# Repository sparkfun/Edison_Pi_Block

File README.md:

SparkFun Edison Pi Block
========================

[*SparkFun Edison GPIO Breakout (DEV-13044)*](https://www.sparkfun.com/products/13038)

The Pi Block is a simple breakout board to bring the GPIO from the Intel Edison to the user. The Block provides level-shifted access to basic GPIO, PWM, UART, I<sup>2</sup>C, and SPI. The pins are presented in the same configuration as a [Raspberry Pi Model B header](http://elinux.org/RPi_Low-level_peripherals#Model_A_and_B_.28Original.29).

Access to the GPIO pins can be accomplished through [MRAA](https://github.com/intel-iot-devkit/mraa). The GPIO number listed on the board or Linux is not the same as MRAA. Refer to the table to see which GPIO pin maps to which number in MRAA. 

*MRAA pin map table based on [Intel's IOT Dev Kit Repository](https://github.com/intel-iot-devkit/mraa/blob/master/docs/edison.md)*

*Pins on the Pi Block are denoted with a * after the GP number*

<table class="table table-bordered">
<thead><tr><th class="text-center" title="Field #1">Edison Pin (Linux)</th>
<th class="text-center" title="Field #2">Arduino Breakout</th>
<th class="text-center" title="Field #3">Mini Breakout</th>
<th class="text-center" title="Field #4">MRAA Number</th>
<th class="text-center" title="Field #5">Pinmode0</th>
<th class="text-center" title="Field #6">Pinmode1</th>
<th class="text-center" title="Field #7">Pinmode2</th>
</tr></thead>
<tbody><tr class="warning" align="center"><td>GP12*</td>
<td>3</td>
<td>J18-7 </td>
<td align="right">20</td>
<td>GPIO-12</td>
<td>PWM0</td>
<td> </td>
</tr>
<tr class="warning" align="center"><td>GP13*</td>
<td>5</td>
<td>J18-1 </td>
<td align="right">14</td>
<td>GPIO-13</td>
<td>PWM1</td>
<td> </td>
</tr>
<tr class="warning" align="center"><td>GP14*</td>
<td>A4</td>
<td>J19-9 </td>
<td align="right">36</td>
<td>GPIO-14</td>
<td> </td>
<td> </td>
</tr>
<tr align="center"><td>GP15</td>
<td> </td>
<td>J20-7 </td>
<td align="right">48</td>
<td>GPIO-15</td>
<td> </td>
<td> </td>
</tr>
<tr class="warning" align="center"><td>GP19*</td>
<td> </td>
<td>J18-6 </td>
<td align="right">19</td>
<td>GPIO-19</td>
<td>I2C-1-SCL</td>
<td> </td>
</tr>
<tr class="warning" align="center"><td>GP20*</td>
<td> </td>
<td>J17-8 </td>
<td align="right">7</td>
<td>GPIO-20</td>
<td>I2C-1-SDA</td>
<td> </td>
</tr>
<tr align="center"><td>GP27</td>
<td> </td>
<td>J17-7 </td>
<td align="right">6</td>
<td>GPIO-27</td>
<td>I2C-6-SCL</td>
<td> </td>
</tr>
<tr align="center"><td>GP28</td>
<td> </td>
<td>J17-9 </td>
<td align="right">8</td>
<td>GPIO-28</td>
<td>I2C-6-SDA</td>
<td> </td>
</tr>
<tr align="center"><td>GP40</td>
<td>13</td>
<td>J19-10 </td>
<td align="right">37</td>
<td>GPIO-40</td>
<td>SSP2_CLK</td>
<td> </td>
</tr>
<tr align="center"><td>GP41</td>
<td>10</td>
<td>J20-10 </td>
<td align="right">51</td>
<td>GPIO-41</td>
<td>SSP2_FS</td>
<td> </td>
</tr>
<tr align="center"><td>GP42</td>
<td>12</td>
<td>J20-9 </td>
<td align="right">50</td>
<td>GPIO-42</td>
<td>SSP2_RXD</td>
<td> </td>
</tr>
<tr align="center"><td>GP43</td>
<td>11</td>
<td>J19-11 </td>
<td align="right">38</td>
<td>GPIO-43</td>
<td>SSP2_TXD</td>
<td> </td>
</tr>
<tr class="warning" align="center"><td>GP44*</td>
<td>A0</td>
<td>J19-4 </td>
<td align="right">31</td>
<td>GPIO-44</td>
<td> </td>
<td> </td>
</tr>
<tr class="warning" align="center"><td>GP45*</td>
<td>A1</td>
<td>J20-4 </td>
<td align="right">45</td>
<td>GPIO-45</td>
<td> </td>
<td> </td>
</tr>
<tr class="warning" align="center"><td>GP46*</td>
<td>A2</td>
<td>J19-5 </td>
<td align="right">32</td>
<td>GPIO-46</td>
<td> </td>
<td> </td>
</tr>
<tr class="warning" align="center"><td>GP47*</td>
<td>A3</td>
<td>J20-5 </td>
<td align="right">46</td>
<td>GPIO-47</td>
<td> </td>
<td> </td>
</tr>
<tr class="warning" align="center"><td>GP48*</td>
<td>7</td>
<td>J19-6 </td>
<td align="right">33</td>
<td>GPIO-48</td>
<td> </td>
<td> </td>
</tr>
<tr align="center"><td>GP49</td>
<td>8</td>
<td>J20-6 </td>
<td align="right">47</td>
<td>GPIO-49</td>
<td> </td>
<td> </td>
</tr>
<tr align="center"><td>GP77</td>
<td> </td>
<td>J19-12 </td>
<td align="right">39</td>
<td>GPIO-77</td>
<td>SD</td>
<td> </td>
</tr>
<tr align="center"><td>GP78</td>
<td> </td>
<td>J20-11 </td>
<td align="right">52</td>
<td>GPIO-78</td>
<td>SD</td>
<td> </td>
</tr>
<tr align="center"><td>GP79</td>
<td> </td>
<td>J20-12 </td>
<td align="right">53</td>
<td>GPIO-79</td>
<td>SD</td>
<td> </td>
</tr>
<tr align="center"><td>GP80</td>
<td> </td>
<td>J20-13 </td>
<td align="right">54</td>
<td>GPIO-80</td>
<td>SD</td>
<td> </td>
</tr>
<tr align="center"><td>GP81</td>
<td> </td>
<td>J20-14 </td>
<td align="right">55</td>
<td>GPIO-81</td>
<td>SD</td>
<td> </td>
</tr>
<tr align="center"><td>GP82</td>
<td> </td>
<td>J19-13 </td>
<td align="right">40</td>
<td>GPIO-82</td>
<td>SD</td>
<td> </td>
</tr>
<tr align="center"><td>GP83</td>
<td> </td>
<td>J19-14 </td>
<td align="right">41</td>
<td>GPIO-83</td>
<td>SD</td>
<td> </td>
</tr>
<tr align="center"><td>GP84</td>
<td> </td>
<td>J20-8 </td>
<td align="right">49</td>
<td>GPIO-84</td>
<td>SD</td>
<td> </td>
</tr>
<tr class="warning" align="center"><td>GP109*</td>
<td> </td>
<td>J17-11 </td>
<td align="right">10</td>
<td>GPIO-109</td>
<td>SPI-5-SCK</td>
<td> </td>
</tr>
<tr class="warning" align="center"><td>GP110*</td>
<td> </td>
<td>J18-10 </td>
<td align="right">23</td>
<td>GPIO-110</td>
<td>SPI-5-CS0</td>
<td> </td>
</tr>
<tr class="warning" align="center"><td>GP111*</td>
<td> </td>
<td>J17-10 </td>
<td align="right">9</td>
<td>GPIO-111</td>
<td>SPI-5-CS1</td>
<td> </td>
</tr>
<tr class="warning" align="center"><td>GP114*</td>
<td> </td>
<td>J18-11 </td>
<td align="right">24</td>
<td>GPIO-114</td>
<td>SPI-5-MISO</td>
<td> </td>
</tr>
<tr class="warning" align="center"><td>GP115*</td>
<td> </td>
<td>J17-12 </td>
<td align="right">11</td>
<td>GPIO-115</td>
<td>SPI-5-MOSI</td>
<td> </td>
</tr>
<tr align="center"><td>GP128</td>
<td>2</td>
<td>J17-14 </td>
<td align="right">13</td>
<td>GPIO-128</td>
<td>UART-1-CTS</td>
<td> </td>
</tr>
<tr align="center"><td>GP129</td>
<td>4</td>
<td>J18-12 </td>
<td align="right">25</td>
<td>GPIO-129</td>
<td>UART-1-RTS</td>
<td> </td>
</tr>
<tr class="warning" align="center"><td>GP130*</td>
<td>0</td>
<td>J18-13 </td>
<td align="right">26</td>
<td>GPIO-130</td>
<td>UART-1-RX</td>
<td> </td>
</tr>
<tr class="warning" align="center"><td>GP131*</td>
<td>1</td>
<td>J19-8 </td>
<td align="right">35</td>
<td>GPIO-131</td>
<td>UART-1-TX</td>
<td> </td>
</tr>
<tr align="center"><td>GP134</td>
<td> </td>
<td>J20-3 </td>
<td align="right">44</td>
<td> </td>
<td> </td>
<td> </td>
</tr>
<tr align="center"><td>GP135</td>
<td> </td>
<td>J17-5 </td>
<td align="right">4</td>
<td>GPIO-135</td>
<td>UART</td>
<td> </td>
</tr>
<tr align="center"><td>GP165</td>
<td>A5</td>
<td>J18-2 </td>
<td align="right">15</td>
<td>GPIO-165</td>
<td> </td>
<td> </td>
</tr>
<tr align="center"><td>GP182</td>
<td>6</td>
<td>J17-1 </td>
<td align="right">0</td>
<td>GPIO-182</td>
<td>PWM2</td>
<td> </td>
</tr>
<tr align="center"><td>GP183</td>
<td>9</td>
<td>J18-8 </td>
<td align="right">21</td>
<td>GPIO-183</td>
<td>PWM3</td>
<td> </td>
</tr>
</tbody></table>

Repository Contents
-------------------
* **/Hardware** - Eagle PCB layout files
* **/Production** - Files to support SparkFun production

Documentation
--------------
* **[Hookup Guide](https://learn.sparkfun.com/tutorials/sparkfun-blocks-for-intel-edison---pi-block)** - Basic hookup guide

Product Versions
----------------
* [DEV-13044](https://www.sparkfun.com/products/13038)- Hardware version 1.0. 

Version History
---------------
* [V_1.0](https://github.com/sparkfun/Edison_Pi_Block/tree/V_1.0) - GitHub files version 1.0

License Information
-------------------

This product is _**open source**_! 

Please review the LICENSE.md file for license information. 

If you have any questions or concerns on licensing, please contact techsupport@sparkfun.com.

Distributed as-is; no warranty is given.

- Your friends at SparkFun.

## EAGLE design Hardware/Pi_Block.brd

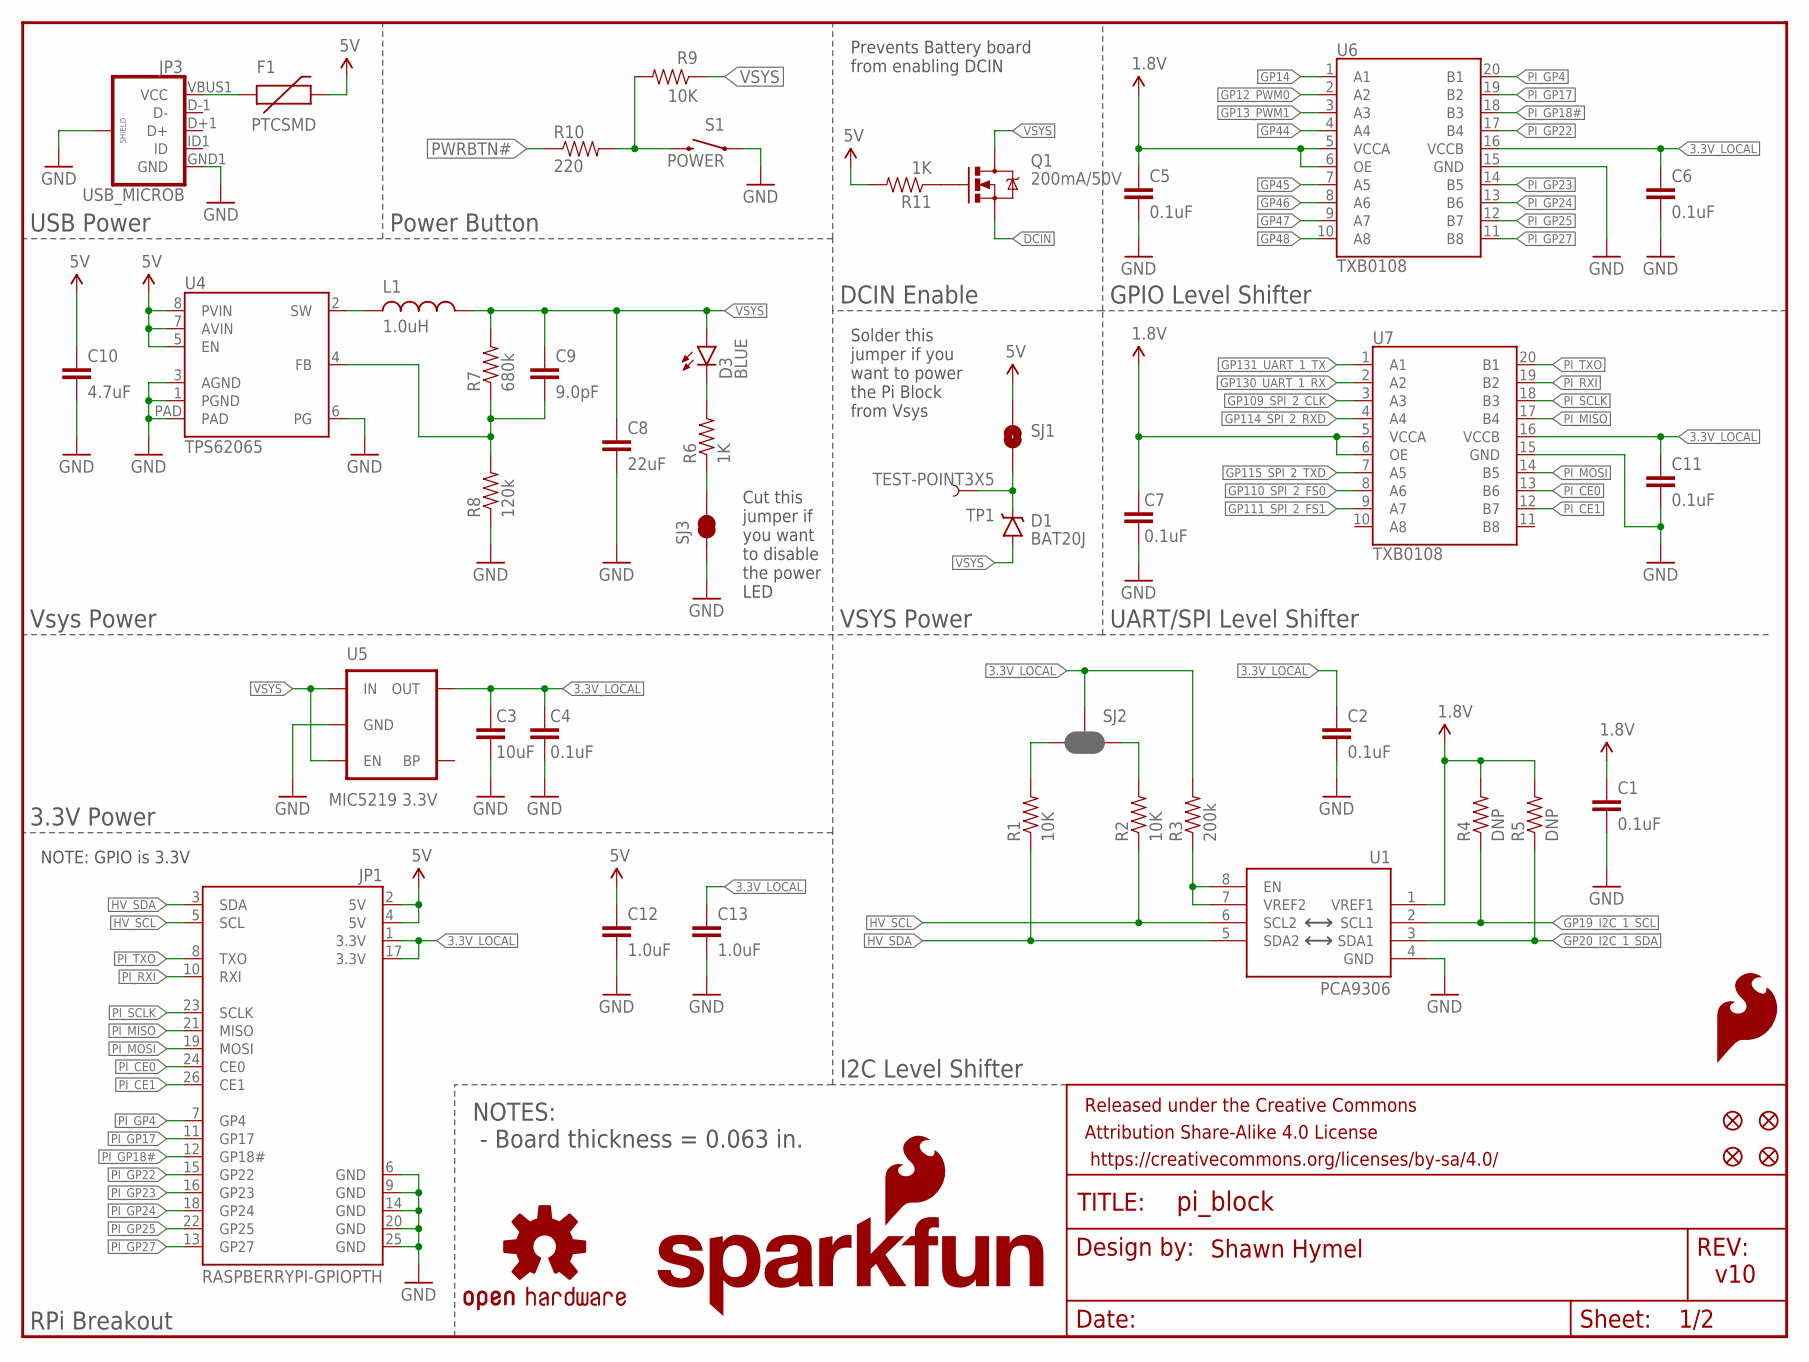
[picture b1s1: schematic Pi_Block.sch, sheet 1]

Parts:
C1, C2, C4, C5, C6, C7, C11: 0.1uF; 0603-CAP
C3: 10uF; 0805
C8: 22uF; 0805
C9: 9.0pF; 0603-CAP
C10: 4.7uF; 0603-CAP
C12, C13: 1.0uF; 0603-CAP
D1: BAT20J; SOD-323
D3: BLUE; LED-0603
F1: PTCSMD; PTC-1206
FID1, FID2, FID3, FID4: FIDUCIAL1X2; FIDUCIAL-1X2
FRAME1, FRAME3: FRAME-LETTER; CREATIVE_COMMONS
JP1: RASPBERRYPI-GPIOPTH; 2X13-SHROUDED
JP3: USB_MICROB; USB-B-MICRO-SMD_V03
L1: 1.0uH; INDUCTOR-SRP4020
LOGO1: OSHW-LOGOS; OSHW-LOGO-S
LOGO3: SFE_LOGO_FLAME.2_INCH; SFE_LOGO_FLAME_.2
LOGO4: SFE_LOGO_NAME_FLAME.1_INCH; SFE_LOGO_NAME_FLAME_.1
Q1: 200mA/50V; SOT23-3
R1, R2, R9: 10K; 0603-RES
R3: 200k; 0603-RES
R4, R5: DNP; 0603-RES
R6, R11: 1K; 0603-RES
R7: 680k; 0603-RES
R8: 120k; 0603-RES
R10: 220; 0603-RES
S1: POWER; TACTILE_SWITCH-SMD-RIGHT-ANGLE
SJ1: JUMPER-PAD-2-NOYES_SILK; PAD-JUMPER-2-NO_YES_SILK
SJ2: JUMPER-PAD-3-NC_BY_PASTE; PAD-JUMPER-3-NC_BY_PASTE_YES_SILK_FULL_BOX
SJ3: JUMPER-PAD-2-NC_BY_TRACE; PAD-JUMPER-2-NC_BY_TRACE_YES_SILK
TP1: TEST-POINT3X5; PAD.03X.05
U1: PCA9306; PCA9306DC-1:1
U4: TPS62065; WSON-8-PAD
U5: MIC5219 3.3V; SOT23-5
U6, U7: TXB0108; UFDFN-20

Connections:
1.8V: C1.1, C5.1, C7.1, R4.2, R5.2, U1.1 (VREF1), U6.5 (VCCA), U6.6 (OE), U7.5 (VCCA), U7.6 (OE); also elsewhere on the board
3.3V_LOCAL: C2.1, C3.1, C4.1, C6.1, C11.1, C13.1, JP1.1 (3.3V), JP1.17 (3.3V), R3.2, SJ2.2, U5.5 (OUT), U6.16 (VCCB), U7.16 (VCCB)
5V: C10.1, C12.1, F1.2, JP1.2 (5V), JP1.4 (5V), R11.2, SJ1.1, U4.5 (EN), U4.7 (AVIN), U4.8 (PVIN)
DCIN: Q1.2 (S); also elsewhere on the board
GND: C1.2, C2.2, C3.2, C4.2, C5.2, C6.2, C7.2, C8.2, C10.2, C11.2, C12.2, C13.2, JP1.6 (GND), JP1.9 (GND), JP1.14 (GND), JP1.20 (GND), JP1.25 (GND), JP3.GND1 (GND), JP3.SHIELD1 (SHIELD), JP3.SHIELD2 (SHIELD), JP3.SHIELD3 (SHIELD), R8.1, S1.1, SJ3.1, U1.4 (GND), U4.1 (PGND), U4.3 (AGND), U4.6 (PG), U4.PAD, U5.2 (GND), U6.15 (GND), U7.15 (GND); also elsewhere on the board
GP12_PWM0: U6.2 (A2); also elsewhere on the board
GP13_PWM1: U6.3 (A3); also elsewhere on the board
GP14: U6.1 (A1); also elsewhere on the board
GP19_I2C_1_SCL: R4.1, U1.2 (SCL1); also elsewhere on the board
GP20_I2C_1_SDA: R5.1, U1.3 (SDA1); also elsewhere on the board
GP44: U6.4 (A4); also elsewhere on the board
GP45: U6.7 (A5); also elsewhere on the board
GP46: U6.8 (A6); also elsewhere on the board
GP47: U6.9 (A7); also elsewhere on the board
GP48: U6.10 (A8); also elsewhere on the board
GP109_SPI_2_CLK: U7.3 (A3); also elsewhere on the board
GP110_SPI_2_FS0: U7.8 (A6); also elsewhere on the board
GP111_SPI_2_FS1: U7.9 (A7); also elsewhere on the board
GP114_SPI_2_RXD: U7.4 (A4); also elsewhere on the board
GP115_SPI_2_TXD: U7.7 (A5); also elsewhere on the board
GP130_UART_1_RX: U7.2 (A2); also elsewhere on the board
GP131_UART_1_TX: U7.1 (A1); also elsewhere on the board
HV_SCL: JP1.5 (SCL), R2.1, U1.6 (SCL2)
HV_SDA: JP1.3 (SDA), R1.1, U1.5 (SDA2)
unnamed: R3.1, U1.7 (VREF2), U1.8 (EN)
unnamed: F1.1, JP3.VBUS1 (VCC)
unnamed: D1.C, SJ1.2, TP1.P$1
unnamed: R1.2, SJ2.3
unnamed: R2.2, SJ2.1
unnamed: D3.C, R6.2
unnamed: R6.1, SJ3.2
unnamed: R9.2, R10.2, S1.2
unnamed: Q1.1 (G), R11.1
unnamed: C9.2, R7.1, R8.2, U4.4 (FB)
unnamed: L1.P$1 (1), U4.2 (SW)
PI_CE0: JP1.24 (CE0), U7.13 (B6)
PI_CE1: JP1.26 (CE1), U7.12 (B7)
PI_GP4: JP1.7 (GP4), U6.20 (B1)
PI_GP17: JP1.11 (GP17), U6.19 (B2)
PI_GP18#: JP1.12 (GP18#), U6.18 (B3)
PI_GP22: JP1.15 (GP22), U6.17 (B4)
PI_GP23: JP1.16 (GP23), U6.14 (B5)
PI_GP24: JP1.18 (GP24), U6.13 (B6)
PI_GP25: JP1.22 (GP25), U6.12 (B7)
PI_GP27: JP1.13 (GP27), U6.11 (B8)
PI_MISO: JP1.21 (MISO), U7.17 (B4)
PI_MOSI: JP1.19 (MOSI), U7.14 (B5)
PI_RXI: JP1.10 (RXI), U7.19 (B2)
PI_SCLK: JP1.23 (SCLK), U7.18 (B3)
PI_TXO: JP1.8 (TXO), U7.20 (B1)
PWRBTN#: R10.1; also elsewhere on the board
VSYS: C8.1, C9.1, D1.A, D3.A, L1.P$2 (2), Q1.3 (D), R7.2, R9.1, U5.1 (IN), U5.3 (EN); also elsewhere on the board

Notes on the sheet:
v10
Shawn Hymel
USB Power
Vsys Power
3.3V Power
RPi Breakout
GPIO Level Shifter
UART/SPI Level Shifter
I2C Level Shifter
Power Button
Prevents Battery board from enabling DCIN
DCIN Enable
VSYS Power
Solder this jumper if you want to power the Pi Block from Vsys
Cut this jumper if you want to disable the power LED
NOTE: GPIO is 3.3V
NOTES: - Board thickness = 0.063 in.

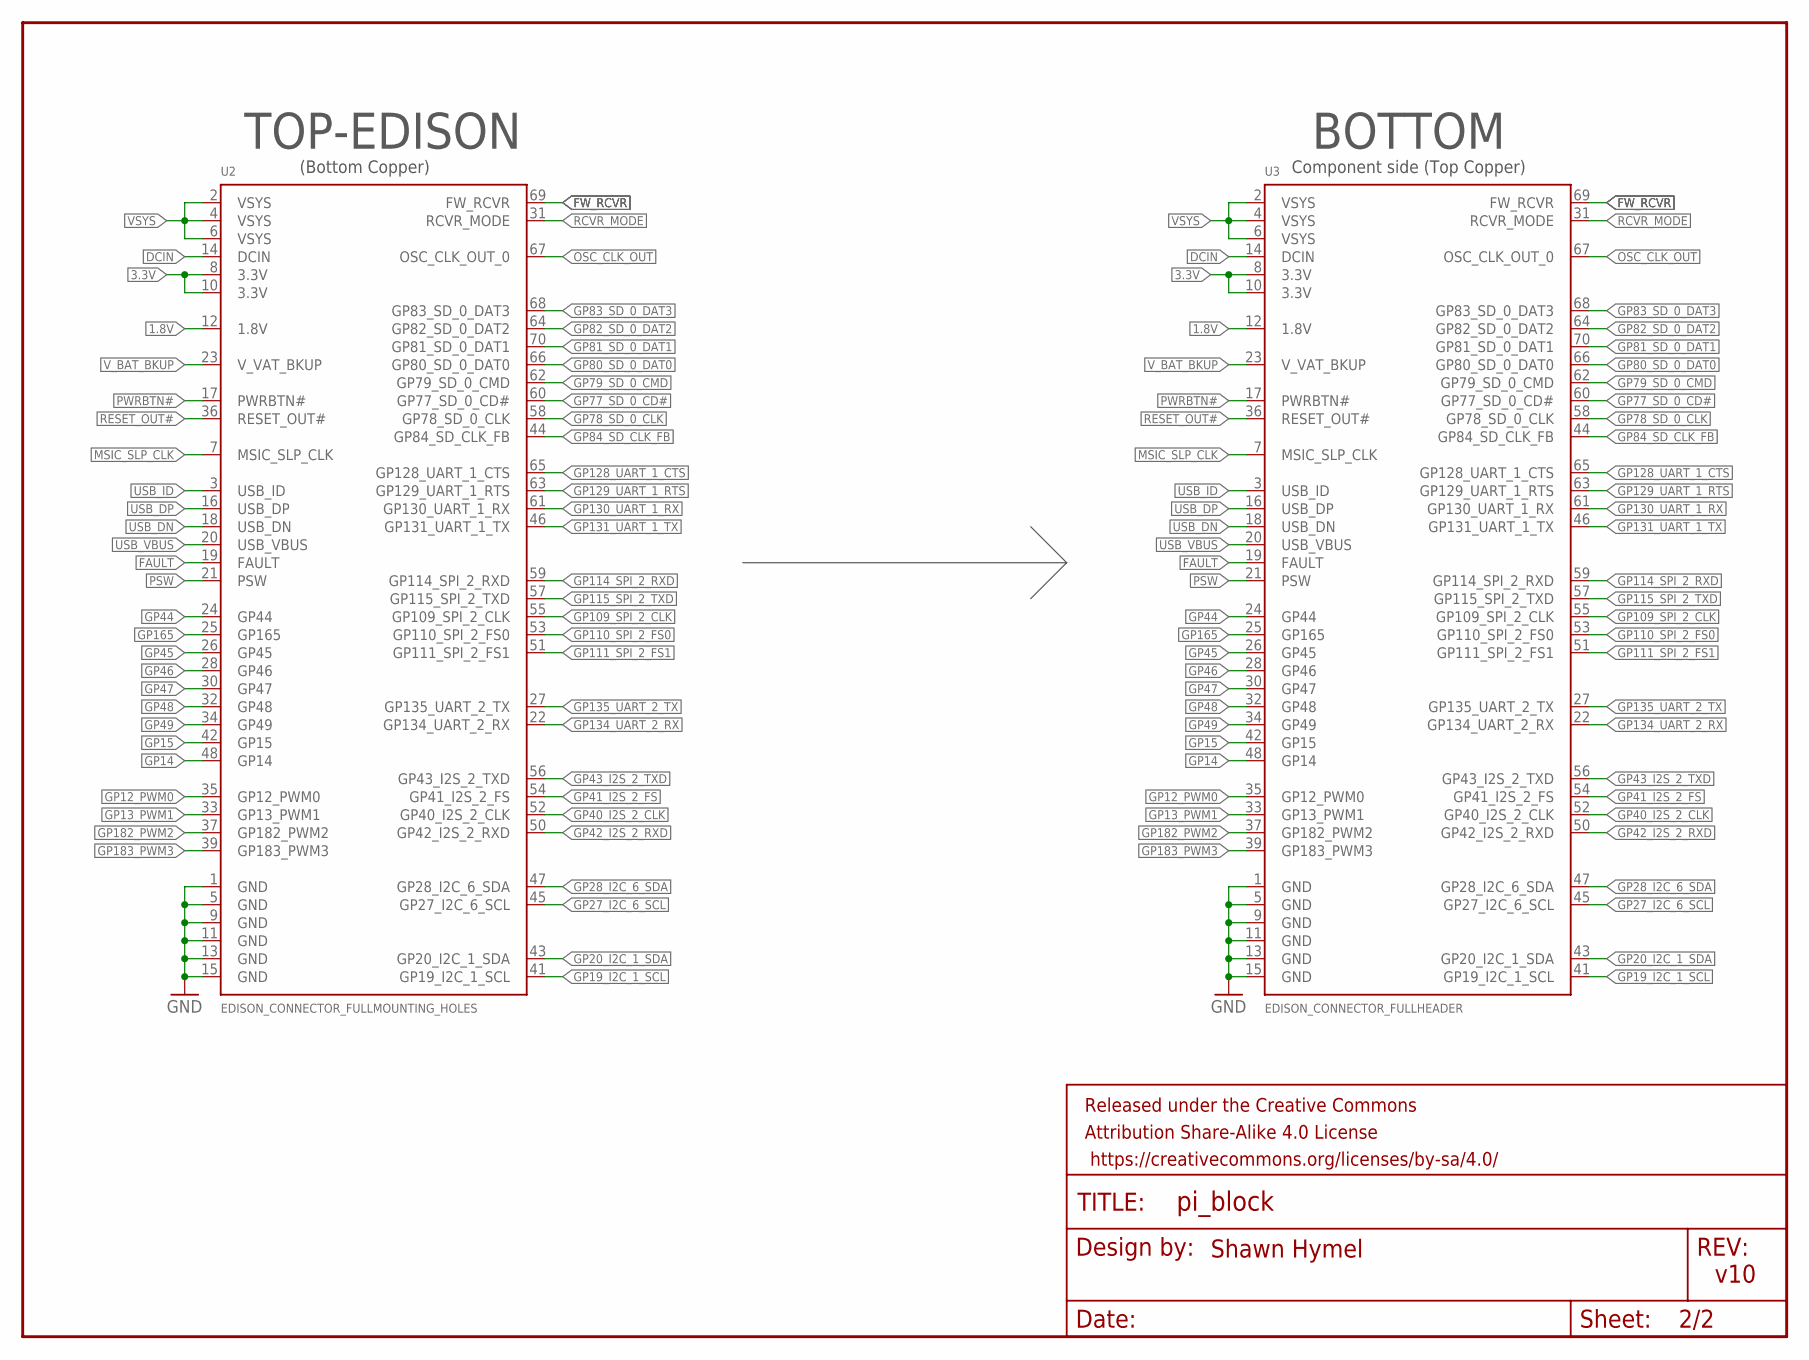
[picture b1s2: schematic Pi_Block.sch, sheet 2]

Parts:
FRAME2: FRAME-LETTER; CREATIVE_COMMONS
U2: EDISON_CONNECTOR_FULLMOUNTING_HOLES; EDISON_DAUGHTER
U3: EDISON_CONNECTOR_FULLHEADER; DF40C-70DP-0.4(51)

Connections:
1.8V: U2.12 (1.8V), U3.12 (1.8V); also elsewhere on the board
3.3V: U2.8 (3.3V), U2.10 (3.3V), U3.8 (3.3V), U3.10 (3.3V)
DCIN: U2.14 (DCIN), U3.14 (DCIN); also elsewhere on the board
FAULT: U2.19 (FAULT), U3.19 (FAULT)
FW_RCVR: U2.69 (FW_RCVR), U3.69 (FW_RCVR)
GND: U2.1 (GND), U2.5 (GND), U2.9 (GND), U2.11 (GND), U2.13 (GND), U2.15 (GND), U3.1 (GND), U3.5 (GND), U3.9 (GND), U3.11 (GND), U3.13 (GND), U3.15 (GND); also elsewhere on the board
GP12_PWM0: U2.35 (GP12_PWM0), U3.35 (GP12_PWM0); also elsewhere on the board
GP13_PWM1: U2.33 (GP13_PWM1), U3.33 (GP13_PWM1); also elsewhere on the board
GP14: U2.48 (GP14), U3.48 (GP14); also elsewhere on the board
GP15: U2.42 (GP15), U3.42 (GP15)
GP19_I2C_1_SCL: U2.41 (GP19_I2C_1_SCL), U3.41 (GP19_I2C_1_SCL); also elsewhere on the board
GP20_I2C_1_SDA: U2.43 (GP20_I2C_1_SDA), U3.43 (GP20_I2C_1_SDA); also elsewhere on the board
GP27_I2C_6_SCL: U2.45 (GP27_I2C_6_SCL), U3.45 (GP27_I2C_6_SCL)
GP28_I2C_6_SDA: U2.47 (GP28_I2C_6_SDA), U3.47 (GP28_I2C_6_SDA)
GP40_I2S_2_CLK: U2.52 (GP40_I2S_2_CLK), U3.52 (GP40_I2S_2_CLK)
GP41_I2S_2_FS: U2.54 (GP41_I2S_2_FS), U3.54 (GP41_I2S_2_FS)
GP42_I2S_2_RXD: U2.50 (GP42_I2S_2_RXD), U3.50 (GP42_I2S_2_RXD)
GP43_I2S_2_TXD: U2.56 (GP43_I2S_2_TXD), U3.56 (GP43_I2S_2_TXD)
GP44: U2.24 (GP44), U3.24 (GP44); also elsewhere on the board
GP45: U2.26 (GP45), U3.26 (GP45); also elsewhere on the board
GP46: U2.28 (GP46), U3.28 (GP46); also elsewhere on the board
GP47: U2.30 (GP47), U3.30 (GP47); also elsewhere on the board
GP48: U2.32 (GP48), U3.32 (GP48); also elsewhere on the board
GP49: U2.34 (GP49), U3.34 (GP49)
GP77_SD_0_CD#: U2.60 (GP77_SD_0_CD#), U3.60 (GP77_SD_0_CD#)
GP78_SD_0_CLK: U2.58 (GP78_SD_0_CLK), U3.58 (GP78_SD_0_CLK)
GP79_SD_0_CMD: U2.62 (GP79_SD_0_CMD), U3.62 (GP79_SD_0_CMD)
GP80_SD_0_DAT0: U2.66 (GP80_SD_0_DAT0), U3.66 (GP80_SD_0_DAT0)
GP81_SD_0_DAT1: U2.70 (GP81_SD_0_DAT1), U3.70 (GP81_SD_0_DAT1)
GP82_SD_0_DAT2: U2.64 (GP82_SD_0_DAT2), U3.64 (GP82_SD_0_DAT2)
GP83_SD_0_DAT3: U2.68 (GP83_SD_0_DAT3), U3.68 (GP83_SD_0_DAT3)
GP84_SD_CLK_FB: U2.44 (GP84_SD_CLK_FB), U3.44 (GP84_SD_CLK_FB)
GP109_SPI_2_CLK: U2.55 (GP109_SPI_2_CLK), U3.55 (GP109_SPI_2_CLK); also elsewhere on the board
GP110_SPI_2_FS0: U2.53 (GP110_SPI_2_FS0), U3.53 (GP110_SPI_2_FS0); also elsewhere on the board
GP111_SPI_2_FS1: U2.51 (GP111_SPI_2_FS1), U3.51 (GP111_SPI_2_FS1); also elsewhere on the board
GP114_SPI_2_RXD: U2.59 (GP114_SPI_2_RXD), U3.59 (GP114_SPI_2_RXD); also elsewhere on the board
GP115_SPI_2_TXD: U2.57 (GP115_SPI_2_TXD), U3.57 (GP115_SPI_2_TXD); also elsewhere on the board
GP128_UART_1_CTS: U2.65 (GP128_UART_1_CTS), U3.65 (GP128_UART_1_CTS)
GP129_UART_1_RTS: U2.63 (GP129_UART_1_RTS), U3.63 (GP129_UART_1_RTS)
GP130_UART_1_RX: U2.61 (GP130_UART_1_RX), U3.61 (GP130_UART_1_RX); also elsewhere on the board
GP131_UART_1_TX: U2.46 (GP131_UART_1_TX), U3.46 (GP131_UART_1_TX); also elsewhere on the board
GP134_UART_2_RX: U2.22 (GP134_UART_2_RX), U3.22 (GP134_UART_2_RX)
GP135_UART_2_TX: U2.27 (GP135_UART_2_TX), U3.27 (GP135_UART_2_TX)
GP165: U2.25 (GP165), U3.25 (GP165)
GP182_PWM2: U2.37 (GP182_PWM2), U3.37 (GP182_PWM2)
GP183_PWM3: U2.39 (GP183_PWM3), U3.39 (GP183_PWM3)
MSIC_SLP_CLK: U2.7 (MSIC_SLP_CLK), U3.7 (MSIC_SLP_CLK)
OSC_CLK_OUT: U2.67 (OSC_CLK_OUT_0), U3.67 (OSC_CLK_OUT_0)
PSW: U2.21 (PSW), U3.21 (PSW)
PWRBTN#: U2.17 (PWRBTN#), U3.17 (PWRBTN#); also elsewhere on the board
RCVR_MODE: U2.31 (RCVR_MODE), U3.31 (RCVR_MODE)
RESET_OUT#: U2.36 (RESET_OUT#), U3.36 (RESET_OUT#)
USB_DN: U2.18 (USB_DN), U3.18 (USB_DN)
USB_DP: U2.16 (USB_DP), U3.16 (USB_DP)
USB_ID: U2.3 (USB_ID), U3.3 (USB_ID)
USB_VBUS: U2.20 (USB_VBUS), U3.20 (USB_VBUS)
VSYS: U2.2 (VSYS), U2.4 (VSYS), U2.6 (VSYS), U3.2 (VSYS), U3.4 (VSYS), U3.6 (VSYS); also elsewhere on the board
V_BAT_BKUP: U2.23 (V_VAT_BKUP), U3.23 (V_VAT_BKUP)

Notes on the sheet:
TOP-EDISON
BOTTOM
Component side (Top Copper)
(Bottom Copper)
v10
Shawn Hymel

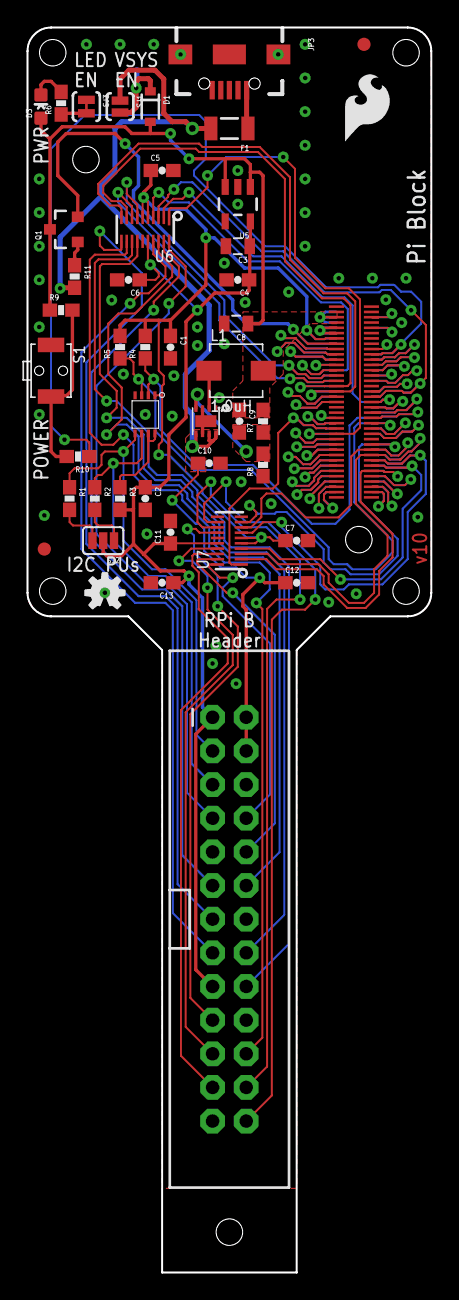
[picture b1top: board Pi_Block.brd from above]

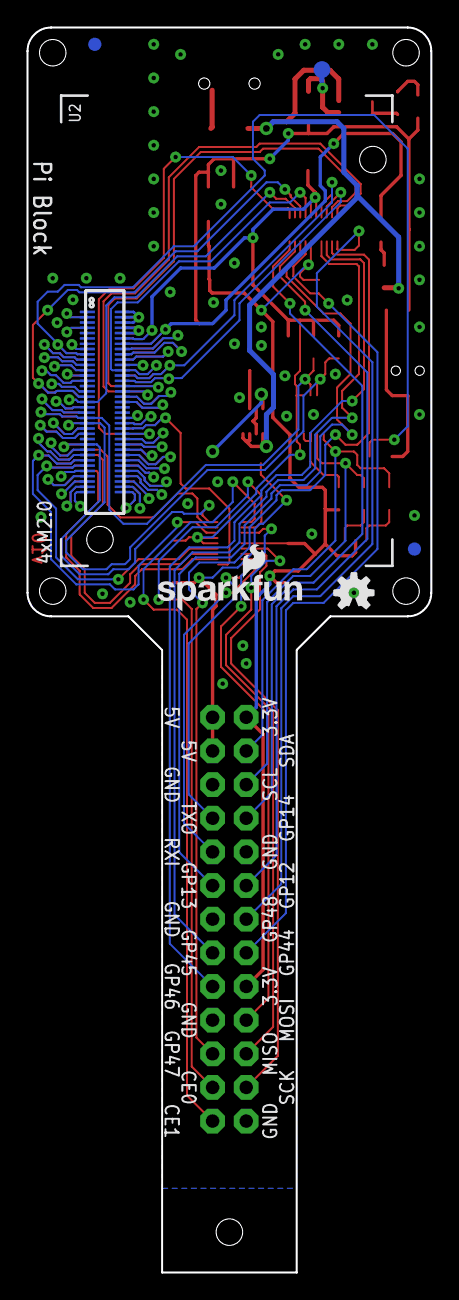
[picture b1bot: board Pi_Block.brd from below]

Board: 2 copper layers, 30.5 x 94.0 mm, 54 parts (7 on the bottom side), 88 nets.

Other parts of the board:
LOGO2: OSHW-LOGOS; OSHW-LOGO-S

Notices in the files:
parts and their libraries:
SparkFun-Aesthetics: Licensing: Creative Commons ShareAlike 4.0 International - https://creativecommons.org/licenses/by-sa/4.0
SparkFun-Aesthetics: Released under the Creative Commons Attribution Share-Alike 4.0 License
SparkFun-Aesthetics: https://creativecommons.org/licenses/by-sa/4.0
